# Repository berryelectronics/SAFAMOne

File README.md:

# SAFAM One | WORK IN PROGRESS
##[FORUM THREAD WITH UPDATES ETC](http://goo.gl/dDuPXW)
##A Simple and Fast Microcontroller
###Based on the STM32F103 Microcontroller
####And the STM32duino Core, build up by Roger Clark, mrburnette, Bobc, victor_pv and many more

This Dev Board is build up around the [STM32F103RET6, a 32-BIT ARM Cortex M3 Microcontroller by STMicroelectronics](http://www.st.com/web/en/resource/technical/document/datasheet/CD00191185.pdf)

It offers a full pinout of the chip with functions, aswell as multiple pinouts of the Serial Communication Pins (SPI, I2C, I2S, UART) aswell as a direct Port for 2.4" Touchscreens and 2.8" Touchscreens.
Also it comes with a break-away Black Magic Probe Clone.

As this Project is still WIP, the schematic and the board will change. 
When the project is finished and you decide to make your own, you're doing it at your own risk. But if the Magic Black Smoke comes up, please report it to me, so i can fix it :)

~Straw/Berryelectronics

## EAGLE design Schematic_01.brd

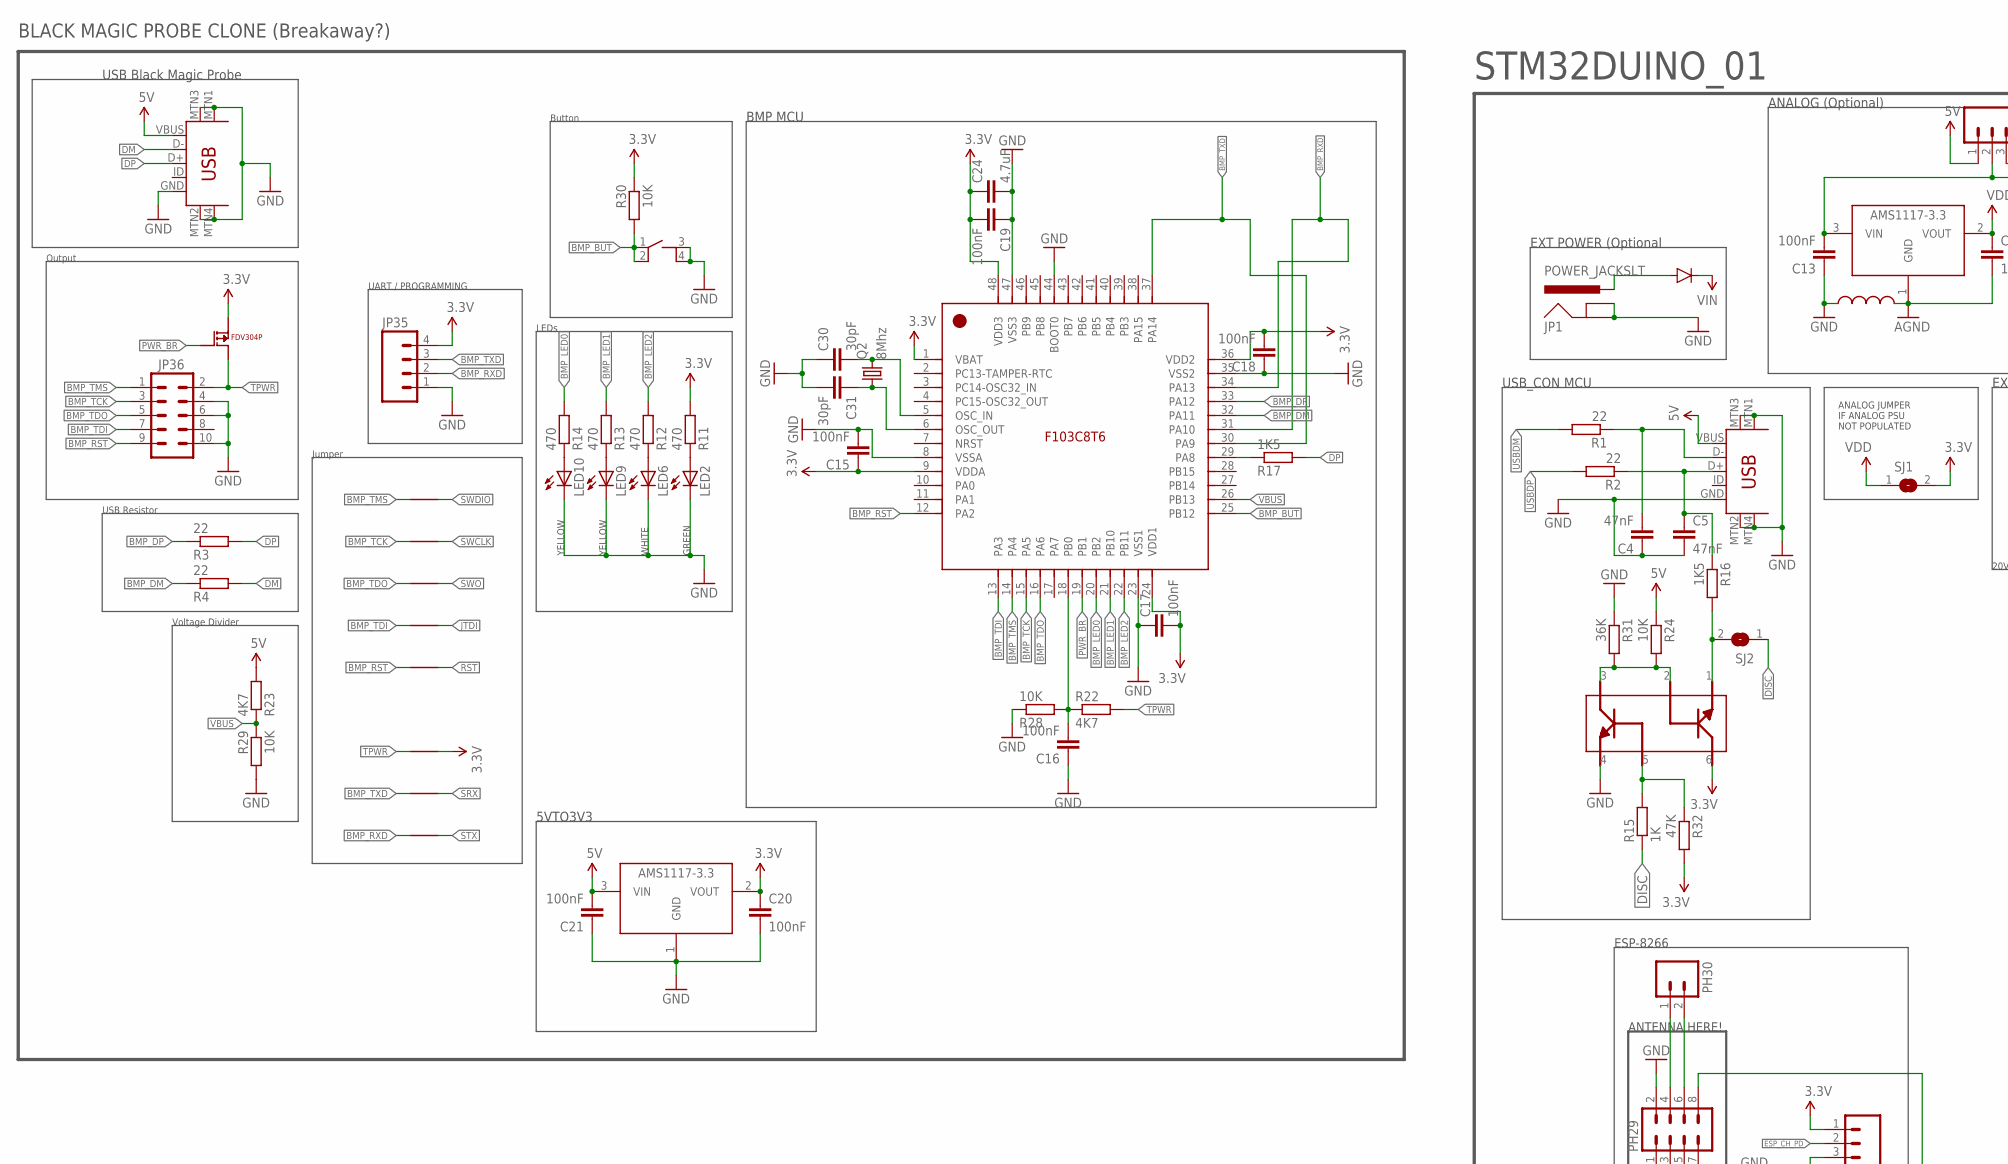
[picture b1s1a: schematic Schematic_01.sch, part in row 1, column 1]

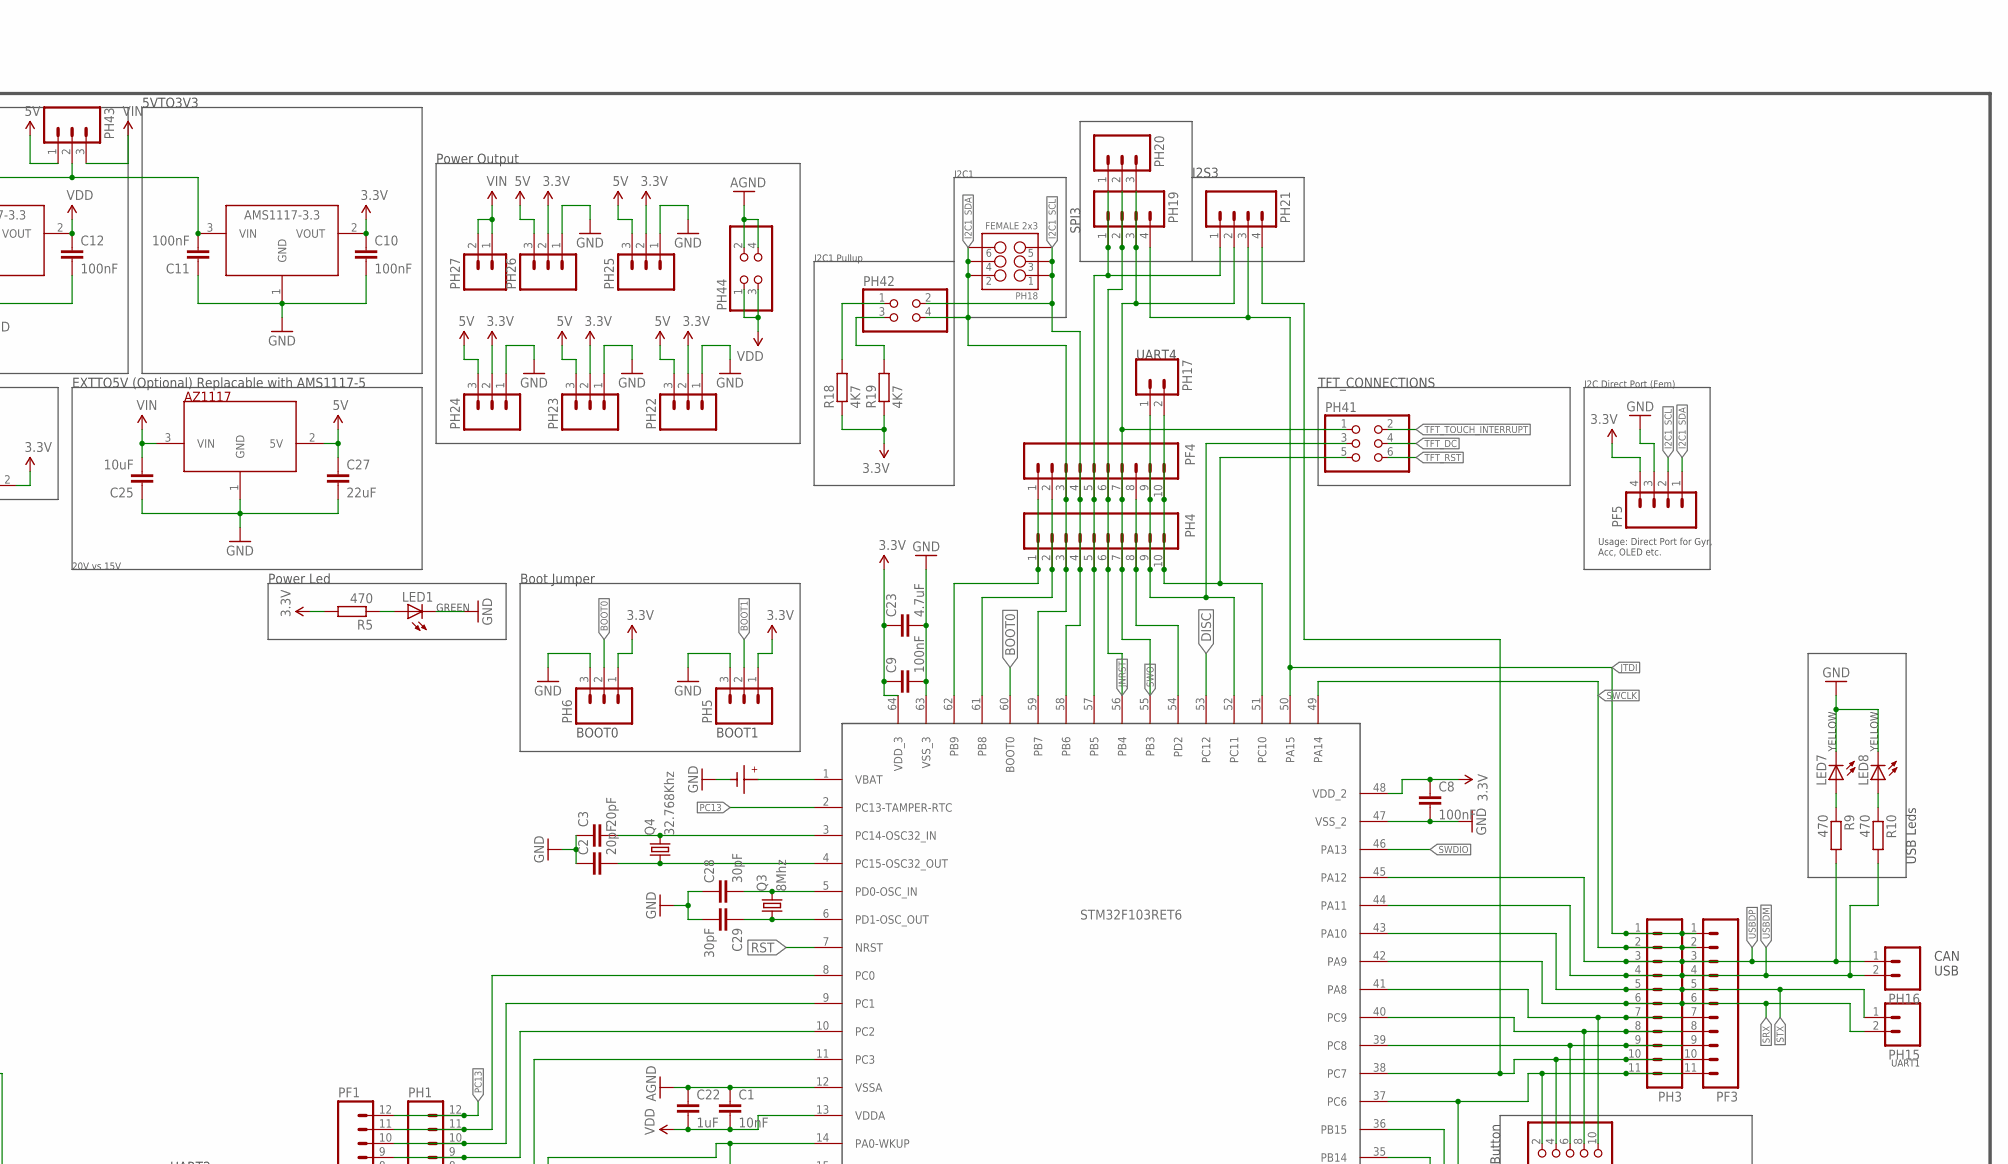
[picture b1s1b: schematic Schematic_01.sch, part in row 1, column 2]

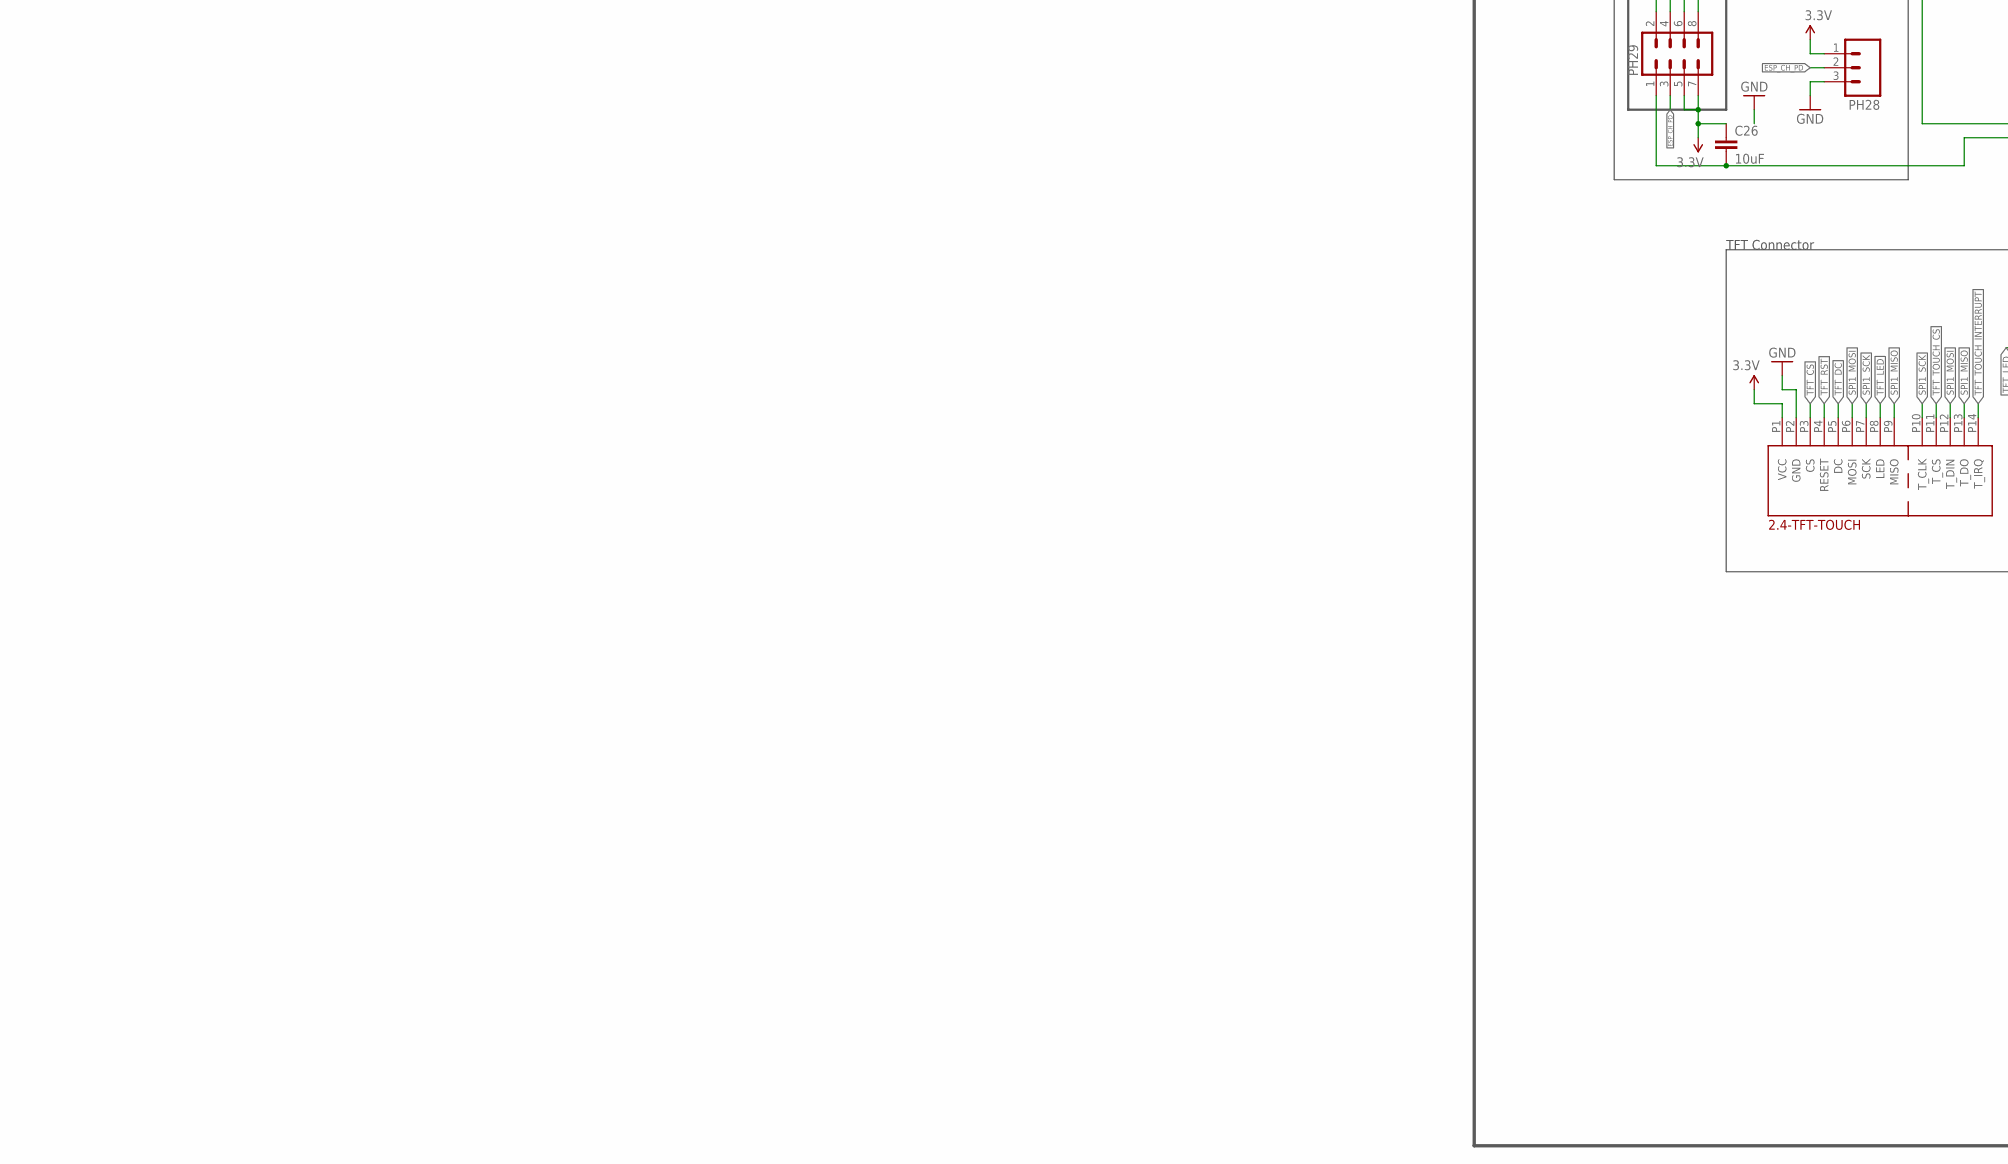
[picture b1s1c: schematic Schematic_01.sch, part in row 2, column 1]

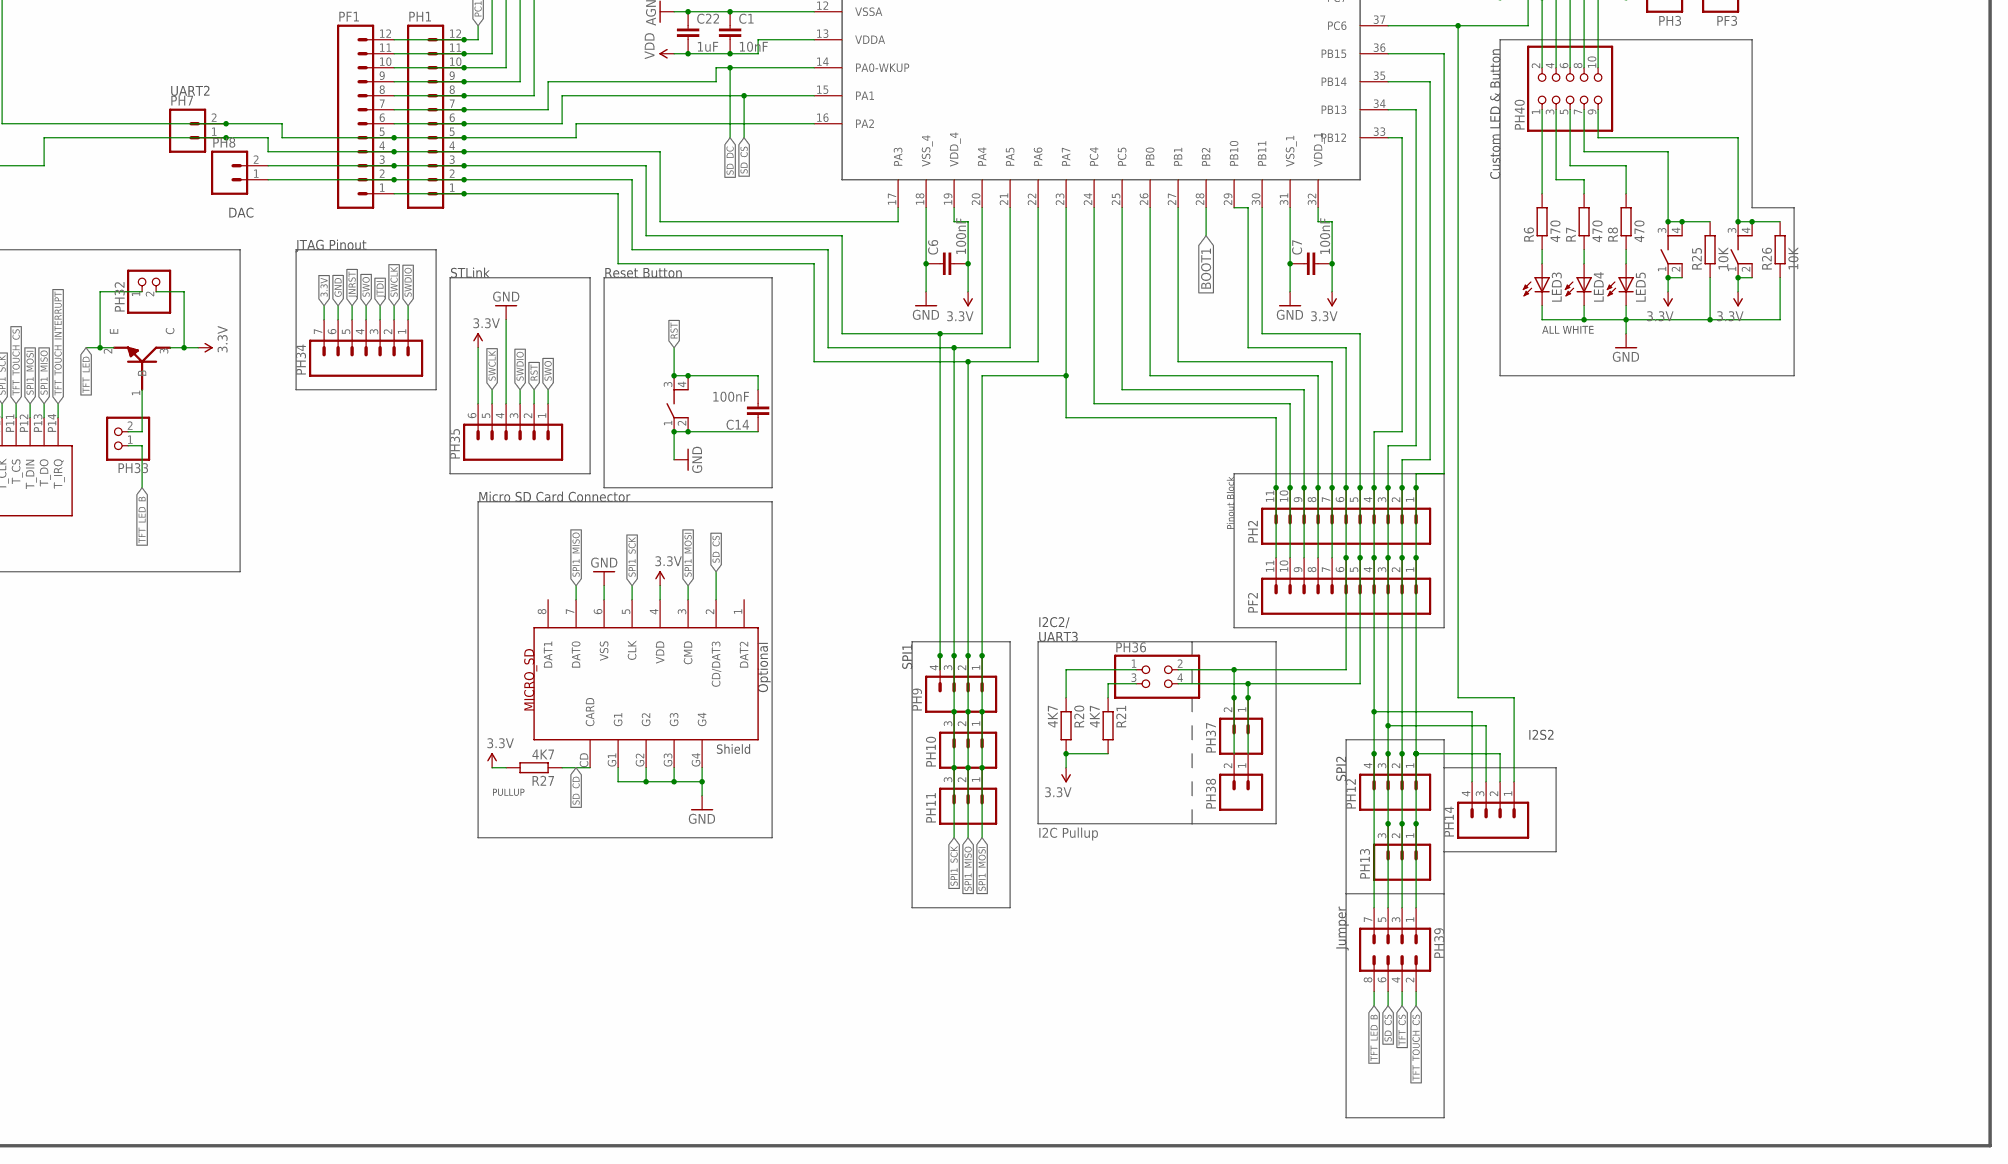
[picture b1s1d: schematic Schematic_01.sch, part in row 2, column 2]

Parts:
C1: 10nF; C0805K
C2, C3: 20pF; C0805K
C4, C5: 47nF; C0805K
C6, C7, C8, C9, C10, C11, C12, C13, C14, C15, C16, C17, C18, C19, C20, C21: 100nF; C0805K
C22: 1uF; C0805K
C23, C24: 4.7uF; C0805K
C25, C26: 10uF; C0805K
C27: 22uF; C0805K
C28, C29, C30, C31: 30pF; C0805K
FB: SMD_FERRITE_BEAD; 0805
JP1: POWER_JACKSLT; POWER_JACK_SLOT
JP35: M04PTH; 1X04
JP36: M05X2PTH; AVR_ICSP
LED1, LED3, LED4, LED5, LED7, LED8: LEDCHIPLED_0805; CHIPLED_0805
LED2, LED6, LED9, LED10: LEDCHIPLED_1206; CHIPLED_1206
PF1: M12PTH; 1X12
PF2, PF3: M11PTH; 1X11
PF4: M10SILK_FEMALE_PTH; 1X10
PF5: M04PTH; 1X04
PH1: M12PTH; 1X12
PH2, PH3: M11PTH; 1X11
PH4: M10SILK_FEMALE_PTH; 1X10
PH5, PH6, PH10, PH11, PH13, PH20, PH22, PH23, PH24, PH25, PH26, PH28, PH43: M03PTH; 1X03
PH7, PH8, PH15, PH16, PH17, PH27, PH30, PH37, PH38: M02PTH; 1X02
PH9, PH12, PH14, PH19, PH21: M04PTH; 1X04
PH18: FEMALE 2x3; 2X3
PH29, PH39: M04X2; 2X4
PH31: TFT-TOUCH
PH32, PH33: PINHD-1X2; 1X02
PH34: M07; 1X07
PH35: M06SILK_FEMALE_PTH; 1X06
PH36, PH42, PH44: PINHD-2X2; 2X02
PH40: PINHD-2X5; 2X05
PH41: PINHD-2X3; 2X03
Q2, Q3: 8Mhz; SM49
Q4: 32.768Khz; MC-306
R1, R2, R3, R4: 22; R0805
R5, R6, R7, R8, R9, R10, R11, R12, R13, R14: 470; R0805
R15: 1K; R0805
R16, R17: 1K5; R0805
R18, R19, R20, R21, R22, R23, R27: 4K7; R0805
R24, R25, R26, R28, R29, R30: 10K; R0805
R31: 36K; R0805
R32: 47K; R0805
SJ1, SJ2: SJ
U1: STM32F103RET6; LQFP64_0.5MMPP
U2: STM32F103C8T6; LQFP48_7X7MM_0.5MMPP
U3, U4, U6: AMS1117-3.3; SOT223
U5: AZ1117-5.0; SOT223
U7: MBT3904DW1T1G; SOT236
U8: BC846A; SOT23-3
U9: FDV304P; SOT23-3
U$1, U$4, U$10, U$15, U$16, U$17, U$18, U$19: BRIDGE
U$2, U$5, U$8, U$9: SMD_BUT_6MM
U$6: CR2025_BATHOLDER_PTH; CR2025HOLDER_PTH
U$7: SD_CARD
U$25: 1N4007_SMD; DO-214AC
USB1, USB2: USB-MINIB-5PIN; USB-MINIB

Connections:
3.3V: C6.2, C7.2, C8.1, C9.1, C10.1, C15.1, C17.2, C18.2, C19.2, C20.1, C23.1, C24.1, C26.1, JP35.4, PF5.4, PH5.1, PH6.1, PH22.2, PH23.2, PH24.2, PH25.2, PH26.2, PH28.1, PH29.5, PH29.7, PH31.P1 (VCC), PH32.2, PH34.7, PH35.6, R5.2, R11.2, R18.1, R19.1, R20.2, R21.2, R27.2, R30.1, R32.2, SJ1.2, U1.19 (VDD_4), U1.32 (VDD_1), U1.48 (VDD_2), U1.64 (VDD_3), U2.1 (VBAT), U2.9 (VDDA), U2.24 (VDD1), U2.36 (VDD2), U2.48 (VDD3), U3.2 (VOUT), U6.2 (VOUT), U7.6, U8.3 (C), U9.2 (S), U$7.4 (VDD), U$8.1, U$8.2, U$9.1, U$9.2, U$10.P$2
5V: C21.2, C27.1, PH22.3, PH23.3, PH24.3, PH25.3, PH26.3, PH43.1, R23.2, R24.1, U5.2 (5V), U6.3 (VIN), USB1.VBUS, USB2.VBUS
AGND: C1.1, C12.2, C22.1, FB.P$4 (2), PH44.2, PH44.4, U1.12 (VSSA), U4.1 (GND)
BMP_BUT: R30.2, U2.25 (PB12), U$2.1, U$2.2
BMP_DM: R4.1, U2.32 (PA11)
BMP_DP: R3.1, U2.33 (PA12)
BMP_LED0: R14.2, U2.20 (PB2)
BMP_LED1: R13.2, U2.21 (PB10)
BMP_LED2: R12.2, U2.22 (PB11)
BMP_RST: JP36.9, U2.12 (PA2), U$15.P$1
BMP_RXD: JP35.2, U2.31 (PA10), U2.34 (PA13), U$1.P$1
BMP_TCK: JP36.3, U2.15 (PA5), U$18.P$1
BMP_TDI: JP36.7, U2.13 (PA3), U$16.P$1
BMP_TDO: JP36.5, U2.16 (PA6), U$17.P$1
BMP_TMS: JP36.1, U2.14 (PA4), U$19.P$1
BMP_TXD: JP35.3, U2.30 (PA9), U2.37 (PA14), U$4.P$1
BOOT0: PH6.2, U1.60 (BOOT0)
BOOT1: PH5.2, U1.28 (PB2)
DISC: R15.1, SJ2.1, U1.53 (PC12)
DM: R4.2, USB2.D-
DP: R3.2, R17.2, USB2.D+
ESP_CH_PD: PH28.2, PH29.3
GND: C2.1, C3.1, C4.1, C5.2, C6.1, C7.1, C8.2, C9.2, C10.2, C11.1, C13.1, C14.1, C15.2, C16.1, C17.1, C18.1, C19.1, C20.2, C21.1, C23.2, C24.2, C25.1, C27.2, C28.1, C29.2, C30.1, C31.2, FB.P$3 (1), JP1.GND@1 (GNDBREAK), JP1.GND@2 (GND), JP35.1, JP36.4, JP36.6, JP36.10, LED1.C, LED2.C, LED3.C, LED4.C, LED5.C, LED6.C, LED7.C, LED8.C, LED9.C, LED10.C, PF5.3, PH5.3, PH6.3, PH22.1, PH23.1, PH24.1, PH25.1, PH26.1, PH28.3, PH29.2, PH31.P2 (GND), PH34.6, PH35.4, R25.1, R26.1, R28.1, R29.2, R31.1, U1.18 (VSS_4), U1.31 (VSS_1), U1.47 (VSS_2), U1.63 (VSS_3), U2.8 (VSSA), U2.23 (VSS1), U2.35 (VSS2), U2.44 (BOOT0), U2.47 (VSS3), U3.1 (GND), U5.1 (GND), U6.1 (GND), U7.4, U$2.3, U$2.4, U$5.1, U$5.2, U$6.BATM, U$7.6 (VSS), U$7.G1, U$7.G2, U$7.G3, U$7.G4, USB1.GND, USB1.MTN1 (MTN2), USB1.MTN2 (MTN3), USB1.MTN3 (MTN1), USB1.MTN4, USB2.GND, USB2.MTN1 (MTN2), USB2.MTN2 (MTN3), USB2.MTN3 (MTN1), USB2.MTN4
I2C1_SCL: PF4.4, PF5.2, PH4.4, PH18.1, PH18.3, PH18.5, PH42.2, U1.58 (PB6)
I2C1_SDA: PF4.3, PF5.1, PH4.3, PH18.2, PH18.4, PH18.6, PH42.4, U1.59 (PB7)
JNRST: PF4.6, PH4.6, PH19.2, PH20.2, PH34.5, U1.56 (PB4)
JTDI: PF3.1, PH3.1, PH19.4, PH21.3, PH34.3, U1.50 (PA15), U$16.P$2
unnamed: LED10.A, R14.1
unnamed: R15.2, R32.1, U7.5
unnamed: PF1.11, PH1.11, U1.8 (PC0)
unnamed: C29.1, Q3.1, U1.6 (PD1-OSC_OUT)
unnamed: PF4.1, PH4.1, U1.62 (PB9)
unnamed: C3.2, Q4.4 (2), U1.3 (PC14-OSC32_IN)
unnamed: PF1.10, PH1.10, U1.9 (PC1)
unnamed: C2.2, Q4.1, U1.4 (PC15-OSC32_OUT)
unnamed: C28.2, Q3.2, U1.5 (PD0-OSC_IN)
unnamed: PF4.2, PH4.2, U1.61 (PB8)
unnamed: LED7.A, R9.1
unnamed: LED8.A, R10.1
unnamed: PF4.5, PH4.5, PH19.1, PH20.1, PH21.1, U1.57 (PB5)
unnamed: PF2.6, PH2.6, PH36.2, PH37.2, PH38.2, U1.29 (PB10)
unnamed: PH40.3, R7.2
unnamed: PF4.8, PH4.8, U1.54 (PD2)
unnamed: PH40.5, R8.2
unnamed: PH36.1, R20.1
unnamed: U1.1 (VBAT), U$6.BATP
unnamed: PH42.1, R18.2
unnamed: PH36.3, R21.1
unnamed: PH42.3, R19.2
unnamed: PF3.7, PH3.7, PH40.10, U1.41 (PA8)
unnamed: PF3.8, PH3.8, PH40.8, U1.40 (PC9)
unnamed: PH33.2, U8.1 (B)
unnamed: PF3.10, PH3.10, PH21.4, PH40.4, U1.38 (PC7)
unnamed: PF3.11, PH3.11, PH14.1, PH40.2, U1.37 (PC6)
unnamed: PF2.5, PH2.5, PH36.4, PH37.1, PH38.1, U1.30 (PB11)
unnamed: R24.2, R31.2, U7.2, U7.3
unnamed: PH29.4, PH30.1
unnamed: PH29.6, PH30.2
unnamed: LED1.A, R5.1
unnamed: PF2.7, PH2.7, U1.27 (PB1)
unnamed: PF2.8, PH2.8, U1.26 (PB0)
unnamed: PF2.9, PH2.9, U1.25 (PC5)
unnamed: PF2.10, PH2.10, U1.24 (PC4)
unnamed: R17.1, U2.29 (PA8)
unnamed: PF1.9, PH1.9, U1.10 (PC2)
unnamed: PF1.8, PH1.8, U1.11 (PC3)
unnamed: R16.2, SJ2.2, U7.1
unnamed: C30.2, Q2.2, U2.5 (OSC_IN)
unnamed: C31.1, Q2.1, U2.6 (OSC_OUT)
unnamed: C26.2, PF1.4, PH1.4, PH7.1, PH29.1, U1.17 (PA3)
unnamed: PF1.3, PH1.3, PH8.2, PH9.4, U1.20 (PA4)
unnamed: LED9.A, R13.1
unnamed: C16.2, R22.1, R28.2, U2.18 (PB0)
unnamed: LED6.A, R12.1
unnamed: LED2.A, R11.1
unnamed: C11.2, C13.2, PH43.2, U3.3 (VIN), U4.3 (VIN)
unnamed: PF3.9, PH3.9, PH40.6, U1.39 (PC8)
unnamed: C4.2, R1.1, USB1.D-
unnamed: PH40.1, R6.2
unnamed: JP1.PWR, U$25.ANODE
unnamed: LED3.A, R6.1
unnamed: LED4.A, R7.1
unnamed: LED5.A, R8.1
unnamed: C5.1, R2.1, R16.1, USB1.D+
unnamed: PH40.9, R26.2, U$9.3, U$9.4
unnamed: PH40.7, R25.2, U$8.3, U$8.4
unnamed: PF4.10, PH4.10, PH17.2, PH41.5, U1.51 (PC10)
unnamed: PF4.9, PH4.9, PH17.1, PH41.3, U1.52 (PC11)
unnamed: PF2.4, PH2.4, PH12.4, PH14.4, PH39.7, U1.33 (PB12)
unnamed: PF2.3, PH2.3, PH12.3, PH13.3, PH14.3, PH39.5, U1.34 (PB13)
unnamed: PF2.2, PH2.2, PH12.2, PH13.2, PH39.3, U1.35 (PB14)
unnamed: PF2.1, PH2.1, PH12.1, PH13.1, PH14.2, PH39.1, U1.36 (PB15)
P%1032: PF1.5, PH1.5, PH7.2, PH29.8, U1.16 (PA2)
PC13: PF1.12, PH1.12, U1.2 (PC13-TAMPER-RTC)
PWR_BR: U2.19 (PB1), U9.1 (G)
RST: C14.2, PH35.2, U1.7 (NRST), U$5.3, U$5.4, U$15.P$2
SD_CD: R27.1, U$7.CD (CARD)
SD_CS: PF1.6, PH1.6, PH39.6, U1.15 (PA1), U$7.2 (CD/DAT3)
SD_DC: PF1.7, PH1.7, U1.14 (PA0-WKUP)
SPI1_MISO: PF1.1, PH1.1, PH9.2, PH10.2, PH11.2, PH31.P9 (MISO), PH31.P13 (T_DO), U1.22 (PA6), U$7.7 (DAT0)
SPI1_MOSI: PF2.11, PH2.11, PH9.1, PH10.1, PH11.1, PH31.P6 (MOSI), PH31.P12 (T_DIN), U1.23 (PA7), U$7.3 (CMD)
SPI1_SCK: PF1.2, PH1.2, PH8.1, PH9.3, PH10.3, PH11.3, PH31.P7 (SCK), PH31.P10 (T_CLK), U1.21 (PA5), U$7.5 (CLK)
SRX: PF3.6, PH3.6, PH15.2, U1.42 (PA9), U$4.P$2
STX: PF3.5, PH3.5, PH15.1, U1.43 (PA10), U$1.P$2
SWCLK: PF3.2, PH3.2, PH34.2, PH35.5, U1.49 (PA14), U$18.P$2
SWDIO: PH34.1, PH35.3, U1.46 (PA13), U$19.P$2
SWO: PF4.7, PH4.7, PH19.3, PH20.3, PH21.2, PH34.4, PH35.1, PH41.1, U1.55 (PB3), U$17.P$2
TFT_CS: PH31.P3 (CS), PH39.4
TFT_DC: PH31.P5 (DC), PH41.4
TFT_LED: PH31.P8 (LED), PH32.1, U8.2 (E)
TFT_LED_B: PH33.1, PH39.8
TFT_RST: PH31.P4 (RESET), PH41.6
TFT_TOUCH_CS: PH31.P11 (T_CS), PH39.2
TFT_TOUCH_INTERRUPT: PH31.P14 (T_IRQ), PH41.2
TPWR: JP36.2, R22.2, U9.3 (D), U$10.P$1
USBDM: PF3.4, PH3.4, PH16.2, R1.2, R10.2, U1.44 (PA11)
USBDP: PF3.3, PH3.3, PH16.1, R2.2, R9.2, U1.45 (PA12)
VBUS: R23.1, R29.1, U2.26 (PB13)
VDD: C1.2, C12.1, C22.2, PH44.1, PH44.3, SJ1.1, U1.13 (VDDA), U4.2 (VOUT)
VIN: C25.2, PH27.1, PH27.2, PH43.3, U5.3 (VIN), U$25.CATHODE

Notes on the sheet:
DAC
UART2
BOOT1
BOOT0
Boot Jumper
Power Output
I2C2/ UART3
SPI1
UART4
CAN USB
SPI3
I2S3
SPI2
I2S2
Reset Button
USB Black Magic Probe
EXT POWER (Optional
5VTO3V3
EXTTO5V (Optional) Replacable with AMS1117-5
I2C Pullup
Shield
ANTENNA HERE!
ESP-8266
ANALOG (Optional)
Optional
ANALOG JUMPER IF ANALOG PSU NOT POPULATED
PULLUP
TFT Connector
Micro SD Card Connector
STLink
Jumper
Custom LED & Button
USB Leds
Power Led
TFT_CONNECTIONS
I2C Direct Port (Fem)
Usage: Direct Port for Gyr, Acc, OLED etc.
I2C1 Pullup
I2C1
Pinout Block

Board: 2 copper layers, 157 parts (33 on the bottom side), 120 nets, no tracks yet.

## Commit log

2015-06-04 :boom::camel: Added .gitattributes & .gitignore files
2015-06-04 Eagle Board Design
2015-06-04 Added Schematic PDF and PNG
2015-06-07 Added a "Somewhat" of an Main Board Layout + PDF and PNG :)

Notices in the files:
parts and their libraries:
SparkFun-Connectors: Licensing: Creative Commons ShareAlike 4.0 International - https://creativecommons.org/licenses/by-sa/4.0
